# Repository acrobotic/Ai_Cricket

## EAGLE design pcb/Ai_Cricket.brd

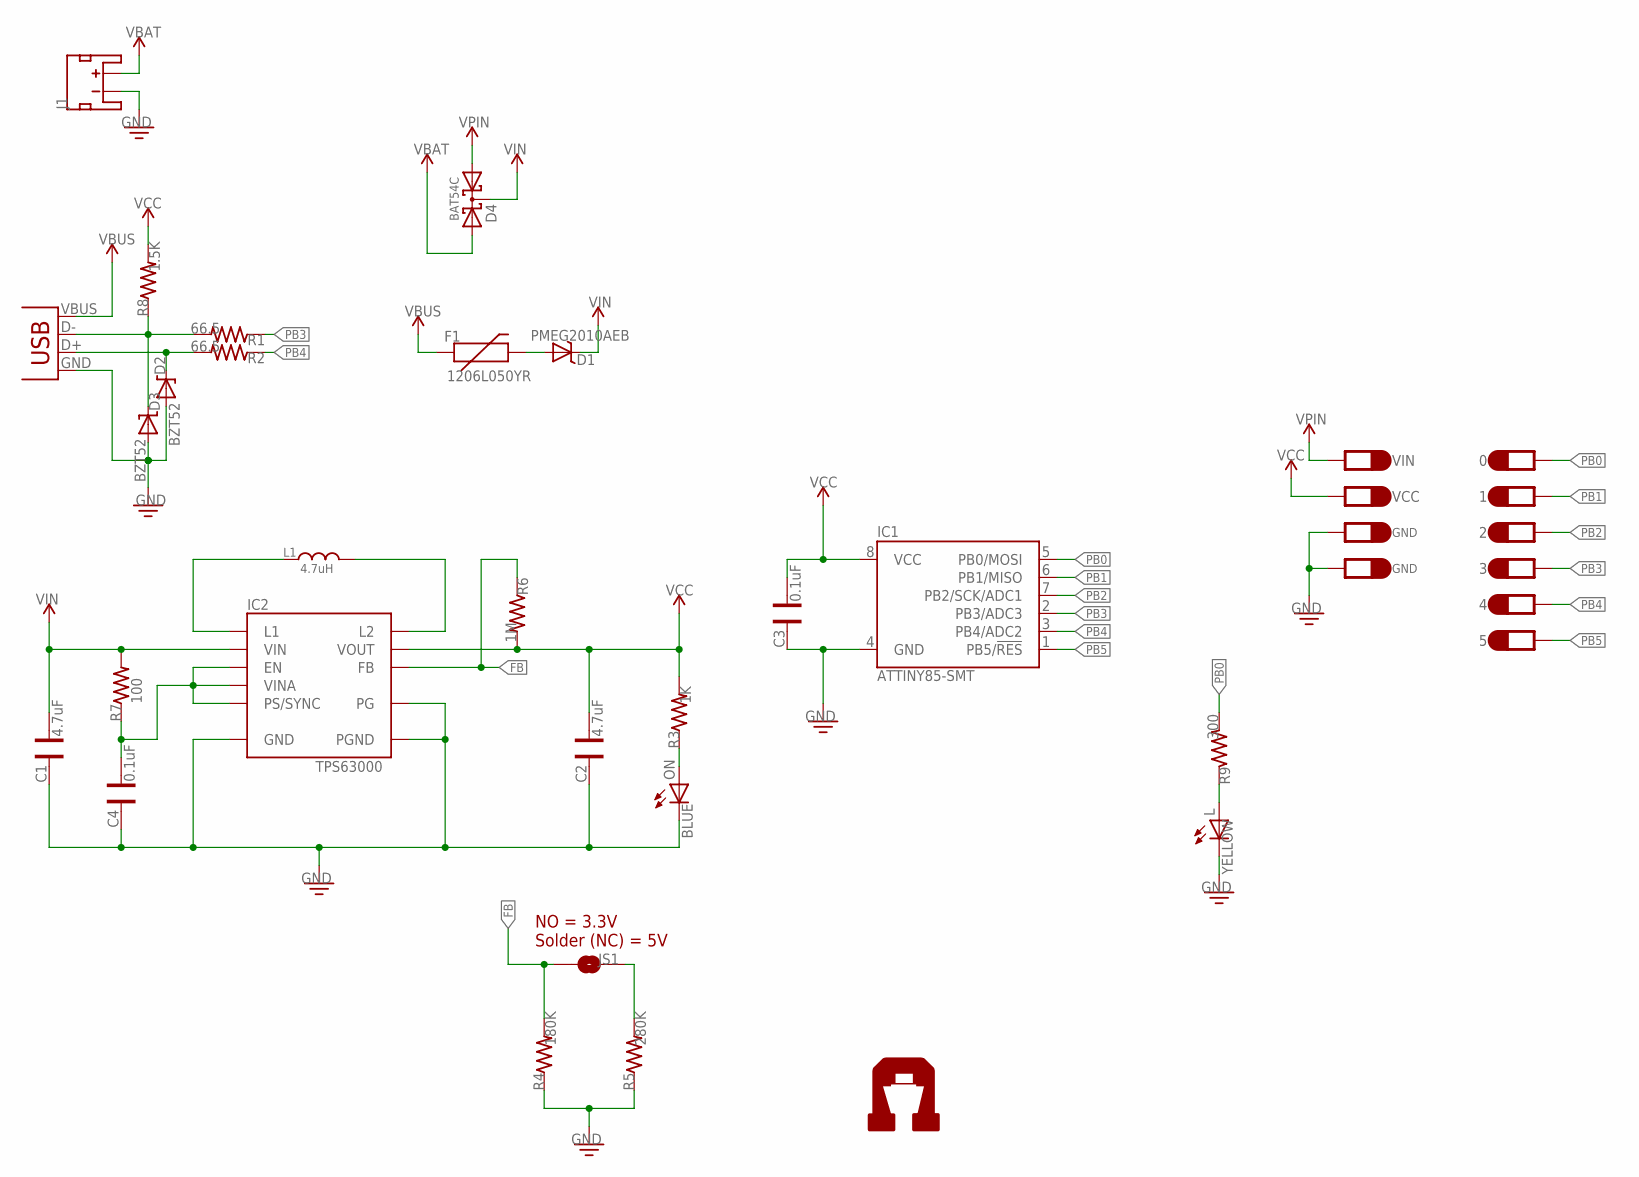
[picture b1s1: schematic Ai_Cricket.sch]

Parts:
0, 1, 2, 3, 4, 5: 1X01-PETAL
C1, C2: 4.7uF; CAP-0402
C3, C4: 0.1uF; CAP-0402
D1: PMEG2010AEB; SOD-523
D2, D3: BZT52; SOD-323
D4: BAT54C; SOT-23
F1: 1206L050YR; PTC-1206
GND7, GND8: 1X01-PETAL
IC1: ATTINY85-SMT; S008-EIAJ
IC2: TPS63000; 10-VFDFN
J1: JST-2-MALE; JST-2-SMD
JS1: 1X02-SJ-NO
L: YELLOW; LED-0603
L1: 4.7uH; IND-0603
ON: BLUE; LED-0603
R1, R2: 66.5; RES-0402
R3: 1K; RES-0402
R4: 180K; RES-0402
R5: 280K; RES-0402
R6: 1M; RES-0402
R7: 100; RES-0402
R8: 1.5K; RES-0402
R9: 300; RES-0402
U$14: AI-LOGOXS; AI-LOGO-XS
USB1: USBMICROB-TH; USB-MICROB-TH
VCC: 1X01-PETAL
VIN: 1X01-PETAL

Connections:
FB: IC2.10 (FB), JS1.1, R4.2, R6.1
GND: C1.2, C2.2, C3.2, C4.2, D2.A, D3.A, GND7.1, GND8.1, IC1.4 (GND), IC2.3 (PGND), IC2.9 (GND), IC2.P$1 (PG), IC2.P$2 (PG), IC2.P$3 (PG), IC2.P$4 (PG), IC2.P$5 (PG), J1.2 (-), L.C, ON.C, R4.1, R5.1, USB1.GND
unnamed: L.A, R9.1
unnamed: IC2.4 (L1), L1.2
unnamed: ON.A, R3.1
unnamed: IC2.2 (L2), L1.1
unnamed: D1.A, F1.2
unnamed: JS1.2, R5.2
unnamed: C4.1, IC2.6 (EN), IC2.7 (PS/SYNC), IC2.8 (VINA), R7.1
unnamed: D3.C, R1.2, R8.1, USB1.D-
unnamed: D2.C, R2.2, USB1.D+
PB0: 0.1, IC1.5 (PB0/MOSI), R9.2
PB1: 1.1, IC1.6 (PB1/MISO)
PB2: 2.1, IC1.7 (PB2/SCK/ADC1)
PB3: 3.1, IC1.2 (PB3/ADC3), R1.1
PB4: 4.1, IC1.3 (PB4/ADC2), R2.1
PB5: 5.1, IC1.1 (PB5/!RES)
VBAT: D4.2 (A2), J1.1 (+)
VBUS: F1.1, USB1.VBUS
VCC: C2.1, C3.1, IC1.8 (VCC), IC2.1 (VOUT), R3.2, R6.2, R8.2, VCC.1
VIN: C1.1, D1.C, D4.3 (CC), IC2.5 (VIN), R7.2
VPIN: D4.1 (A1), VIN.1

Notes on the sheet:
NO = 3.3V Solder (NC) = 5V
GND

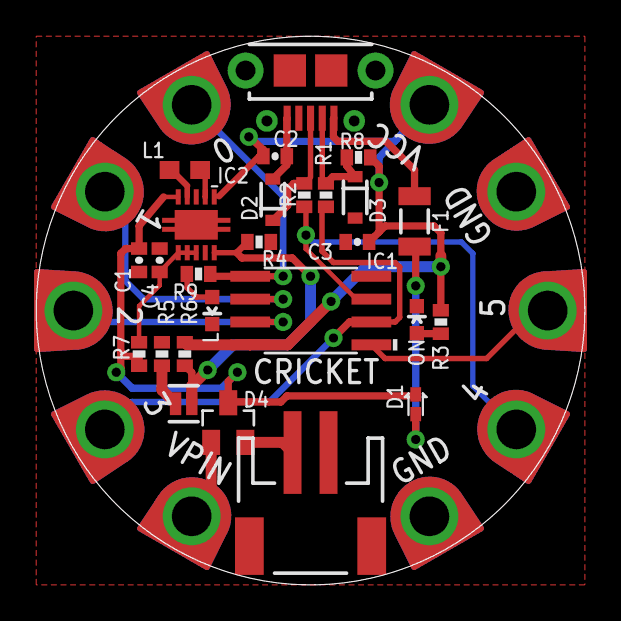
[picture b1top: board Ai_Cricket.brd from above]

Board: 2 copper layers, 30.5 x 30.5 mm, 37 parts (1 on the bottom side), 22 nets.

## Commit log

2014-09-03 v1.0
2014-09-04 updating and sending out to manufacture
2014-09-05 deleting legacy files
2014-09-05 updating
2014-09-05 renaming siliness 1
2014-09-05 renaming silliness part 2
